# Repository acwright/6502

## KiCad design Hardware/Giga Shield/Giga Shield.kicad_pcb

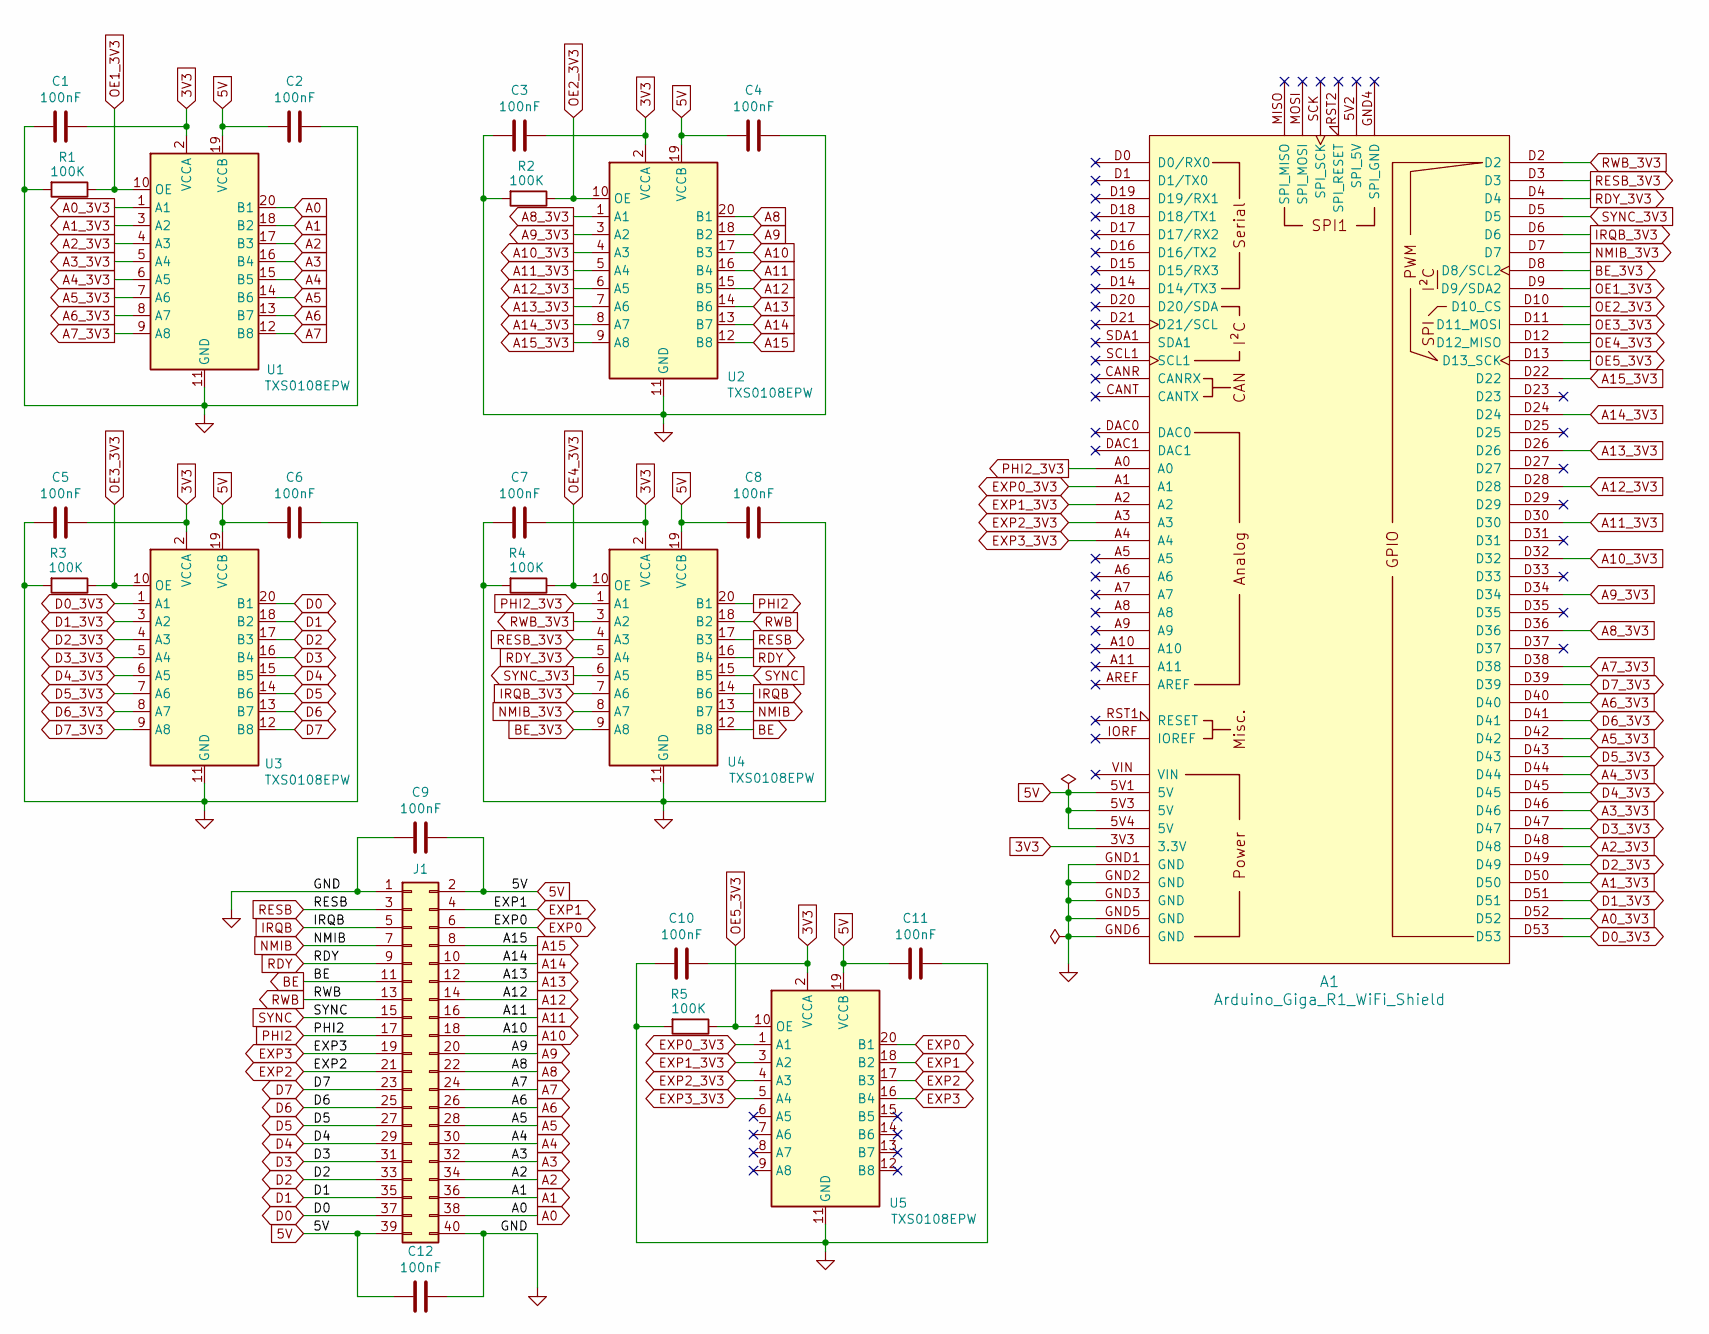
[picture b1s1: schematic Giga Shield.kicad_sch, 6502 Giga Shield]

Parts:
A1: Arduino_Giga_R1_WiFi_Shield
C1, C2, C3, C4, C5, C6, C7, C8, C9, C10, C11, C12: 100nF; C_0805_2012Metric; LCSC C49678
J1: Conn_02x20_Odd_Even; PinHeader_2x20_P2.54mm_Vertical
R1, R2, R3, R4, R5: 100K; R_0805_2012Metric; LCSC C149504
U1, U2, U3, U4, U5: TXS0108EPW; TSSOP-20_4.4x6.5mm_P0.65mm; LCSC C17206

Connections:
3V3: A1.3V3 (3.3V), C1.1, C3.1, C5.1, C7.1, C10.1, U1.2 (VCCA), U2.2 (VCCA), U3.2 (VCCA), U4.2 (VCCA), U5.2 (VCCA)
5V: A1.5V1 (5V), A1.5V3 (5V), A1.5V4 (5V), C2.2, C4.2, C6.2, C8.2, C9.1, C11.2, C12.2, J1.2, J1.39, U1.19 (VCCB), U2.19 (VCCB), U3.19 (VCCB), U4.19 (VCCB), U5.19 (VCCB)
A0: J1.38, U1.20 (B1)
A0_3V3: A1.D52, U1.1 (A1)
A1: J1.36, U1.18 (B2)
A1_3V3: A1.D50, U1.3 (A2)
A2: J1.34, U1.17 (B3)
A2_3V3: A1.D48, U1.4 (A3)
A3: J1.32, U1.16 (B4)
A3_3V3: A1.D46, U1.5 (A4)
A4: J1.30, U1.15 (B5)
A4_3V3: A1.D44, U1.6 (A5)
A5: J1.28, U1.14 (B6)
A5_3V3: A1.D42, U1.7 (A6)
A6: J1.26, U1.13 (B7)
A6_3V3: A1.D40, U1.8 (A7)
A7: J1.24, U1.12 (B8)
A7_3V3: A1.D38, U1.9 (A8)
A8: J1.22, U2.20 (B1)
A8_3V3: A1.D36, U2.1 (A1)
A9: J1.20, U2.18 (B2)
A9_3V3: A1.D34, U2.3 (A2)
A10: J1.18, U2.17 (B3)
A10_3V3: A1.D32, U2.4 (A3)
A11: J1.16, U2.16 (B4)
A11_3V3: A1.D30, U2.5 (A4)
A12: J1.14, U2.15 (B5)
A12_3V3: A1.D28, U2.6 (A5)
A13: J1.12, U2.14 (B6)
A13_3V3: A1.D26, U2.7 (A6)
A14: J1.10, U2.13 (B7)
A14_3V3: A1.D24, U2.8 (A7)
A15: J1.8, U2.12 (B8)
A15_3V3: A1.D22, U2.9 (A8)
BE: J1.11, U4.12 (B8)
BE_3V3: A1.D8 (D8/SCL2), U4.9 (A8)
D0: J1.37, U3.20 (B1)
D0_3V3: A1.D53, U3.1 (A1)
D1: J1.35, U3.18 (B2)
D1_3V3: A1.D51, U3.3 (A2)
D2: J1.33, U3.17 (B3)
D2_3V3: A1.D49, U3.4 (A3)
D3: J1.31, U3.16 (B4)
D3_3V3: A1.D47, U3.5 (A4)
D4: J1.29, U3.15 (B5)
D4_3V3: A1.D45, U3.6 (A5)
D5: J1.27, U3.14 (B6)
D5_3V3: A1.D43, U3.7 (A6)
D6: J1.25, U3.13 (B7)
D6_3V3: A1.D41, U3.8 (A7)
D7: J1.23, U3.12 (B8)
D7_3V3: A1.D39, U3.9 (A8)
EXP0: J1.6, U5.20 (B1)
EXP0_3V3: A1.A1, U5.1 (A1)
EXP1: J1.4, U5.18 (B2)
EXP1_3V3: A1.A2, U5.3 (A2)
EXP2: J1.21, U5.17 (B3)
EXP2_3V3: A1.A3, U5.4 (A3)
EXP3: J1.19, U5.16 (B4)
EXP3_3V3: A1.A4, U5.5 (A4)
GND: A1.GND1 (GND), A1.GND2 (GND), A1.GND3 (GND), A1.GND5 (GND), A1.GND6 (GND), C1.2, C2.1, C3.2, C4.1, C5.2, C6.1, C7.2, C8.1, C9.2, C10.2, C11.1, C12.1, J1.1, J1.40, R1.2, R2.2, R3.2, R4.2, R5.2, U1.11 (GND), U2.11 (GND), U3.11 (GND), U4.11 (GND), U5.11 (GND)
IRQB: J1.5, U4.14 (B6)
IRQB_3V3: A1.D6, U4.7 (A6)
NMIB: J1.7, U4.13 (B7)
NMIB_3V3: A1.D7, U4.8 (A7)
OE1_3V3: A1.D9 (D9/SDA2), R1.1, U1.10 (OE)
OE2_3V3: A1.D10 (D10_CS), R2.1, U2.10 (OE)
OE3_3V3: A1.D11 (D11_MOSI), R3.1, U3.10 (OE)
OE4_3V3: A1.D12 (D12_MISO), R4.1, U4.10 (OE)
OE5_3V3: A1.D13 (D13_SCK), R5.1, U5.10 (OE)
PHI2: J1.17, U4.20 (B1)
PHI2_3V3: A1.A0, U4.1 (A1)
RDY: J1.9, U4.16 (B4)
RDY_3V3: A1.D4, U4.5 (A4)
RESB: J1.3, U4.17 (B3)
RESB_3V3: A1.D3, U4.4 (A3)
RWB: J1.13, U4.18 (B2)
RWB_3V3: A1.D2, U4.3 (A2)
SYNC: J1.15, U4.15 (B5)
SYNC_3V3: A1.D5, U4.6 (A5)

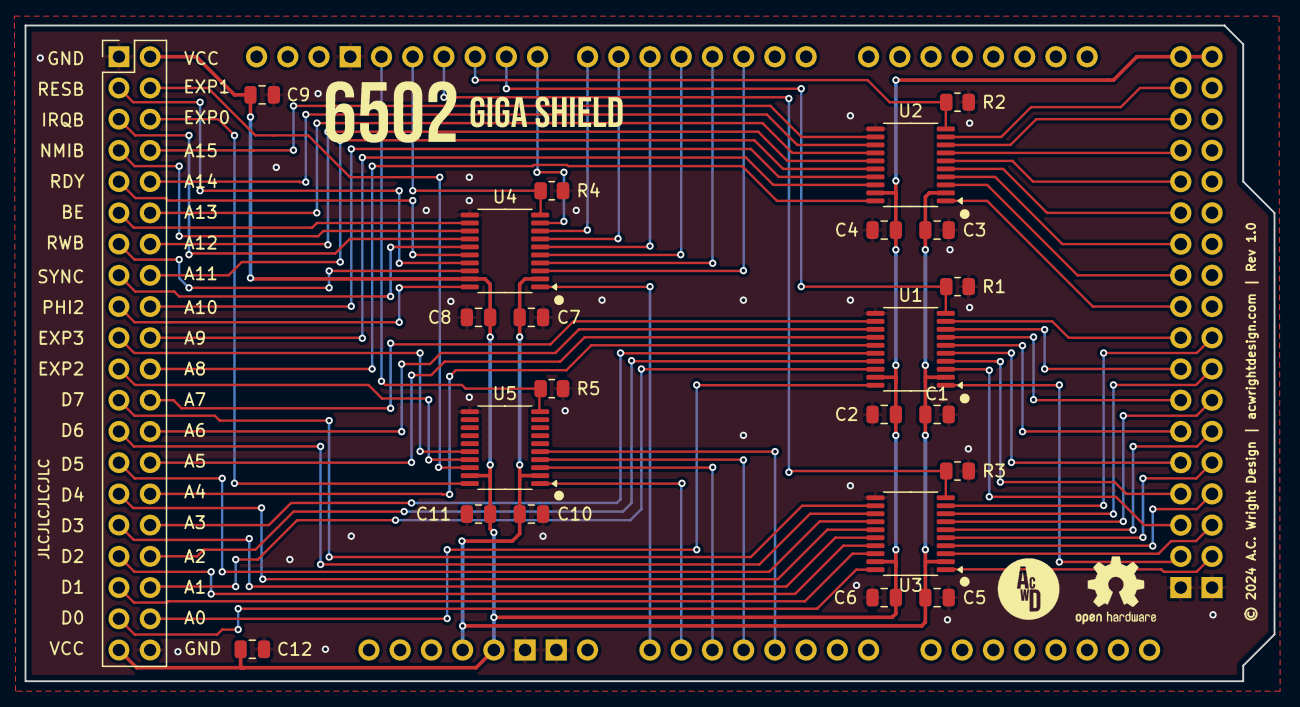
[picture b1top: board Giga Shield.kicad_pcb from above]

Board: 2 copper layers, 101.6 x 53.3 mm, 24 parts (0 on the bottom side), 80 nets.

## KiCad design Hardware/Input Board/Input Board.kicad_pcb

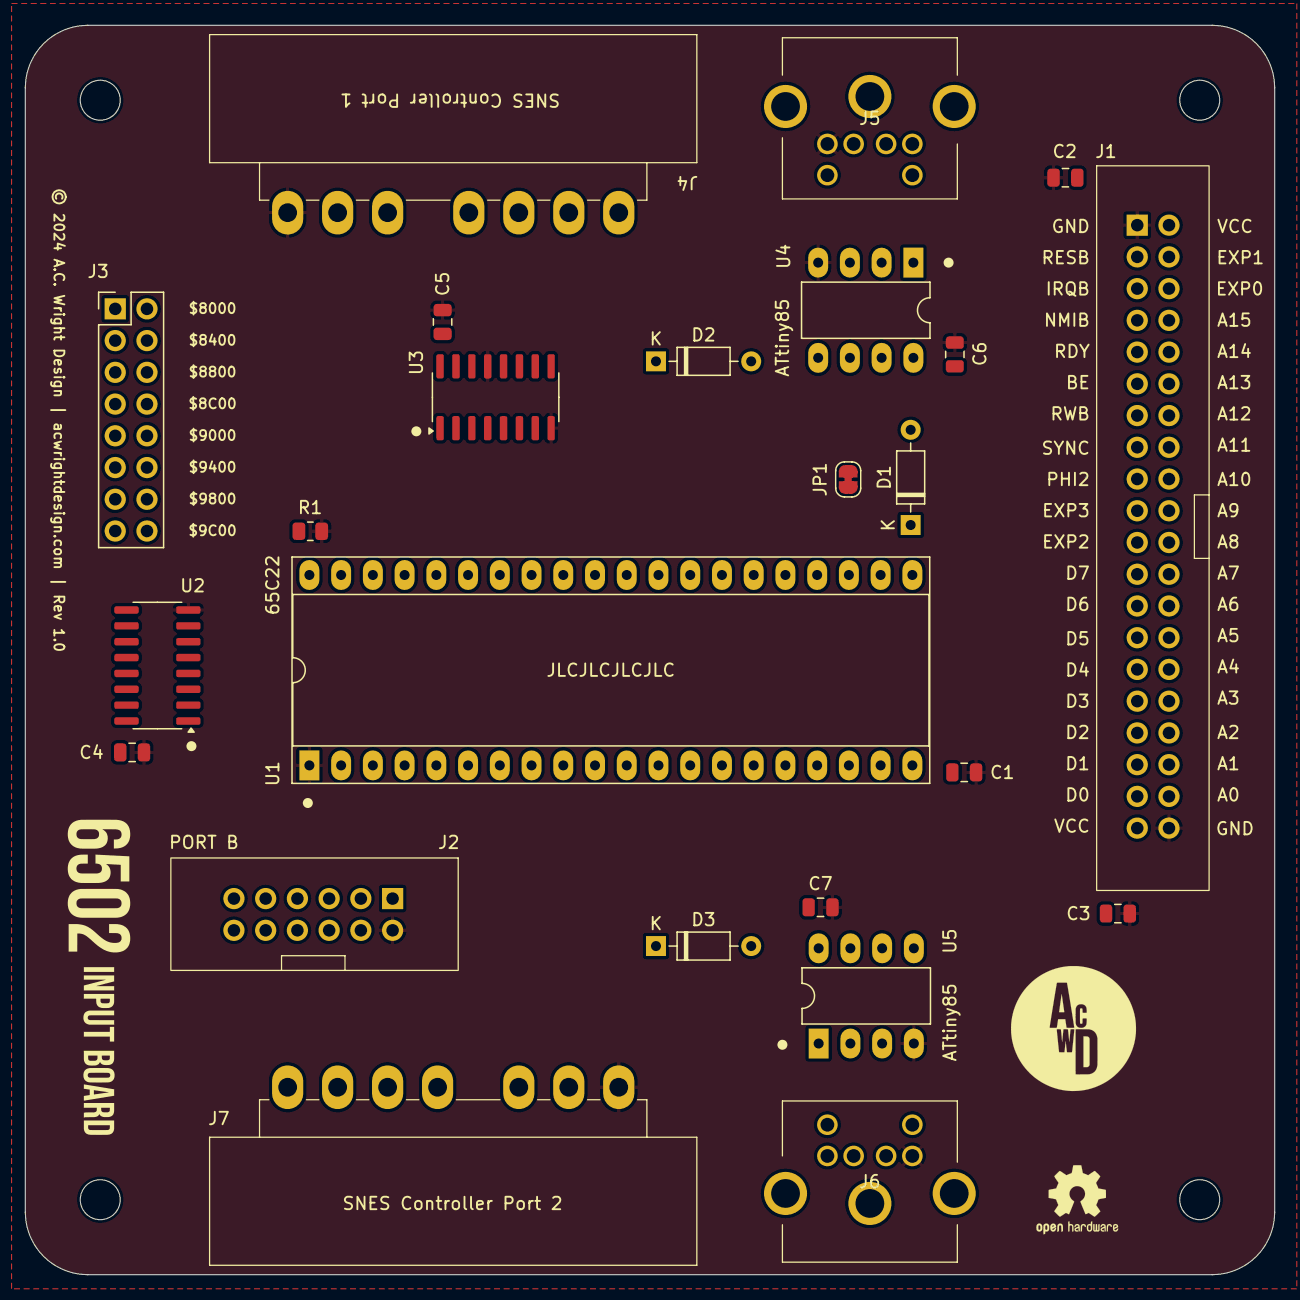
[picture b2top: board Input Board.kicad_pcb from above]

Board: 2 copper layers, 100.0 x 100.0 mm, 28 parts (0 on the bottom side), 62 nets.

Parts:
C1, C2, C3, C4, C5, C6, C7: 100nF; C_0805_2012Metric
D1, D2, D3: D_Schottky; D_DO-35_SOD27_P7.62mm_Horizontal
H1, H2, H3, H4: MountingHole; MountingHole_3.2mm_M3
J1: 6502 Bus; 6502 Bus Connector
J2: PORT B; 6502 GPIO Connector
J3: Conn_02x08_Odd_Even; PinHeader_2x08_P2.54mm_Vertical
J4: SNES Controller Port 1; SNES Controller Port
J5: Keyboard; KMDGX-6S-BS
J6: Mouse; KMDGX-6S-BS
J7: SNES Controller Port 2; SNES Controller Port
JP1: SolderJumper_2_Bridged; SolderJumper-2_P1.3mm_Bridged_RoundedPad1.0x1.5mm
R1: 10k; R_0805_2012Metric
U1: 65C22; DIP-40_W15.24mm_Socket_LongPads
U2: 74HC138; SOIC-16_3.9x9.9mm_P1.27mm
U3: 74HC595; SOIC-16_3.9x9.9mm_P1.27mm
U4, U5: ATtiny85; DIP-8_W7.62mm_LongPads

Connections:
/$8C00: J3.7, U2.12 (~Y3)
/$9C00: J3.15, U2.7 (~Y7)
/$8000: J3.1, U2.15 (~Y0)
/$8400: J3.3, U2.14 (~Y1)
/$8800: J3.5, U2.13 (~Y2)
/$9000: J3.9, U2.11 (~Y4)
/$9400: J3.11, U2.10 (~Y5)
/$9800: J3.13, U2.9 (~Y6)
A0: J1.38, U1.38 (RS0)
A1: J1.36, U1.37 (RS1)
A2: J1.34, U1.36 (RS2)
A3: J1.32, U1.35 (RS3)
A10: J1.18, U2.1 (A0)
A11: J1.16, U2.2 (A1)
A12: J1.14, U2.3 (A2)
A13: J1.12, U2.4 (~E0)
A14: J1.10, U2.5 (~E1)
A15: J1.8, U2.6 (E2)
CA2: U1.39 (CA2), U4.1 (~RESET/PB5), U5.1 (~RESET/PB5)
CB1: J2.11, U1.18 (CB1)
CB2: J2.12, U1.19 (CB2)
CLK: U3.11 (SRCLK), U3.12 (RCLK), U4.5 (AREF/PB0), U5.5 (AREF/PB0)
CSB: J3.2, J3.4, J3.6, J3.8, J3.10, J3.12, J3.14, J3.16, U1.23 (CS2B)
D0: J1.37, U1.33 (D0)
D1: J1.35, U1.32 (D1)
D2: J1.33, U1.31 (D2)
D3: J1.31, U1.30 (D3)
D4: J1.29, U1.29 (D4)
D5: J1.27, U1.28 (D5)
D6: J1.25, U1.27 (D6)
D7: J1.23, U1.26 (D7)
DATA: U3.14 (SER), U4.6 (PB1), U5.6 (PB1)
GND: C1.1, C2.2, C3.1, C4.2, C5.2, C6.2, C7.2, J1.1, J1.40, J2.2, J4.7 (GND), J5.3, J6.3, J7.7 (GND), R1.2, U1.1 (VSS), U2.8 (GND), U3.8 (GND), U3.13 (~OE), U4.4 (GND), U5.4 (GND)
IRQB: D1.2 (A), J1.5, JP1.2 (B)
KBD_CLK: J5.6, U4.7 (PB2)
KBD_DATA: J5.1, U4.2 (XTAL1/PB3)
KBD_INT: D2.2 (A), U4.3 (XTAL2/PB4)
MS_CLK: J6.6, U5.7 (PB2)
MS_DATA: J6.1, U5.2 (XTAL1/PB3)
MS_INT: D3.2 (A), U5.3 (XTAL2/PB4)
unnamed: D1.1 (K), JP1.1 (A), U1.21 (IRQB)
unnamed: D2.1 (K), D3.1 (K), R1.1, U1.40 (CA1)
PA0: U1.2 (PA0), U3.15 (QA)
PA1: U1.3 (PA1), U3.1 (QB)
PA2: U1.4 (PA2), U3.2 (QC)
PA3: U1.5 (PA3), U3.3 (QD)
PA4: U1.6 (PA4), U3.4 (QE)
PA5: U1.7 (PA5), U3.5 (QF)
PA6: U1.8 (PA6), U3.6 (QG)
PA7: U1.9 (PA7), U3.7 (QH)
PB0: J2.4, J4.2 (Clock), J7.2 (Clock), U1.10 (PB0)
PB1: J2.6, J4.3 (Latch), J7.3 (Latch), U1.11 (PB1)
PB2: J2.8, J4.4 (Data), U1.12 (PB2)
PB3: J2.10, J7.4 (Data), U1.13 (PB3)
PB4: J2.9, U1.14 (PB4)
PB5: J2.7, U1.15 (PB5)
PB6: J2.5, U1.16 (PB6)
PB7: J2.3, U1.17 (PB7)
PHI2: J1.17, U1.25 (PHI2)
RESB: J1.3, U1.34 (RESB)
RWB: J1.13, U1.22 (RWB)
VCC: C1.2, C2.1, C3.2, C4.1, C5.1, C6.1, C7.1, J1.2, J1.39, J2.1, J4.1 (VCC), J5.5, J6.5, J7.1 (VCC), U1.20 (VDD), U1.24 (CS1), U2.16 (VCC), U3.10 (~SRCLR), U3.16 (VCC), U4.8 (VCC), U5.8 (VCC)

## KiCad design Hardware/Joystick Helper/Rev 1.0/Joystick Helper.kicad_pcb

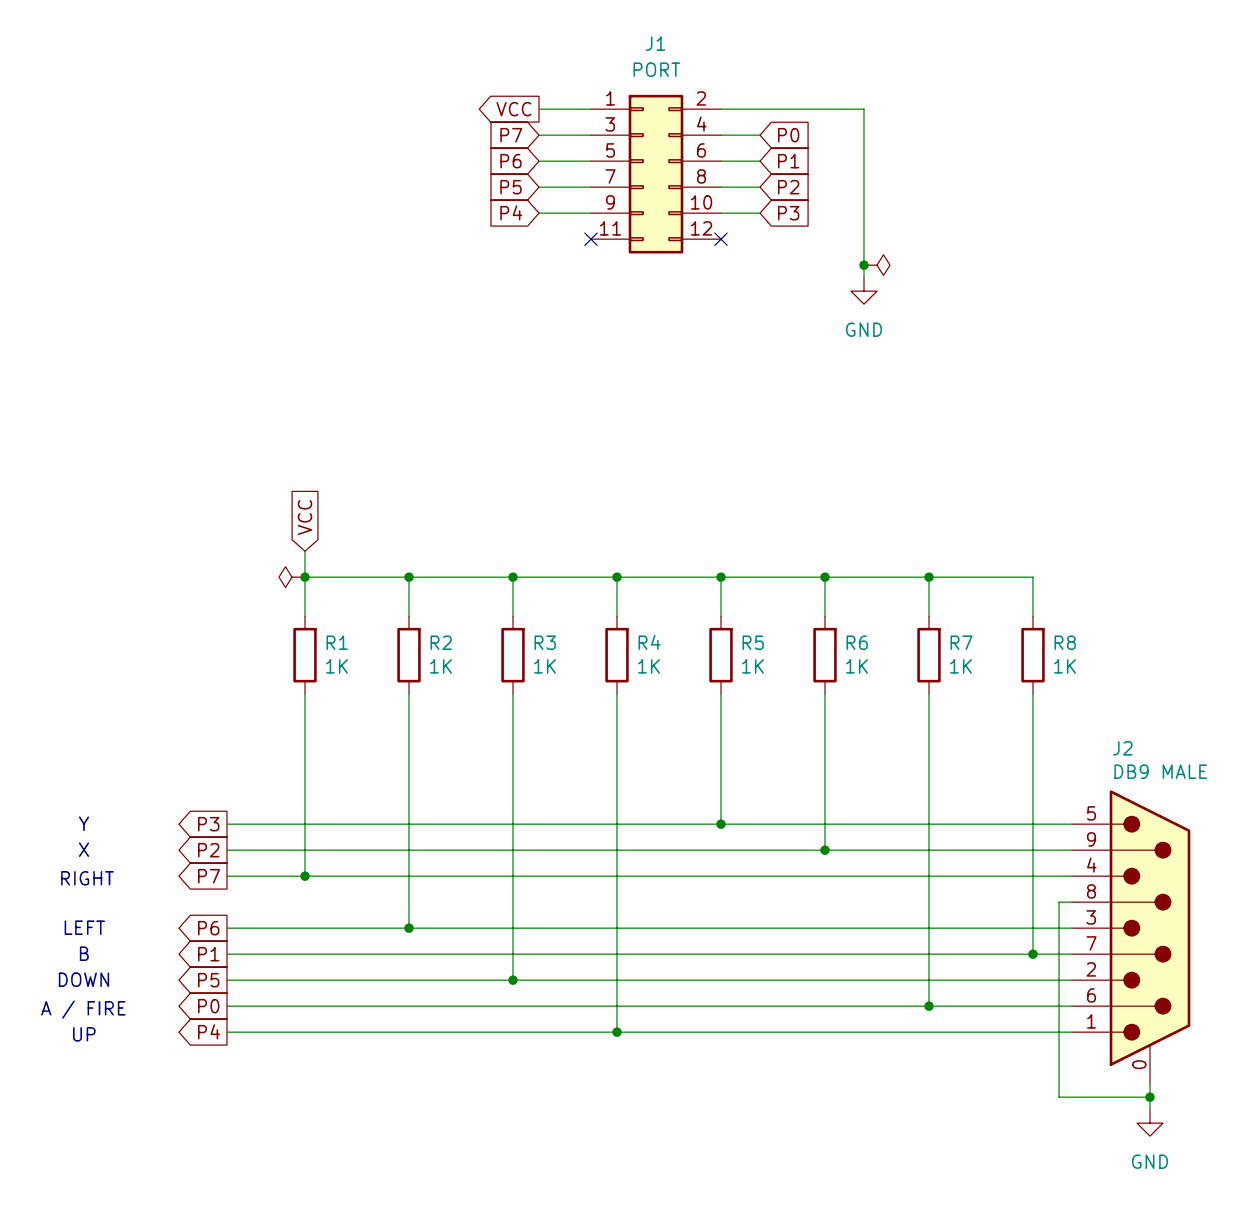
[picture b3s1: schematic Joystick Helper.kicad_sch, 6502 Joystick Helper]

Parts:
J1: PORT; 6502 GPIO Connector
J2: DB9 MALE; DSUB-9_Pins_Horizontal_P2.77x2.84mm_EdgePinOffset7.70mm_Hou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; MPN D09P33E4GX00LF; Digikey 609-1481-ND
R1, R2, R3, R4, R5, R6, R7, R8: 1K; R_Axial_DIN0204_L3.6mm_D1.6mm_P5.08mm_Horizontal

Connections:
GND: J1.2, J2.0 (PAD), J2.8
P0: J1.4, J2.6, R7.1
P1: J1.6, J2.7, R8.1
P2: J1.8, J2.9, R6.1
P3: J1.10, J2.5, R5.1
P4: J1.9, J2.1, R4.1
P5: J1.7, J2.2, R3.1
P6: J1.5, J2.3, R2.1
P7: J1.3, J2.4, R1.1
VCC: J1.1, R1.2, R2.2, R3.2, R4.2, R5.2, R6.2, R7.2, R8.2

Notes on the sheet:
LEFT
DOWN
RIGHT
A / FIRE

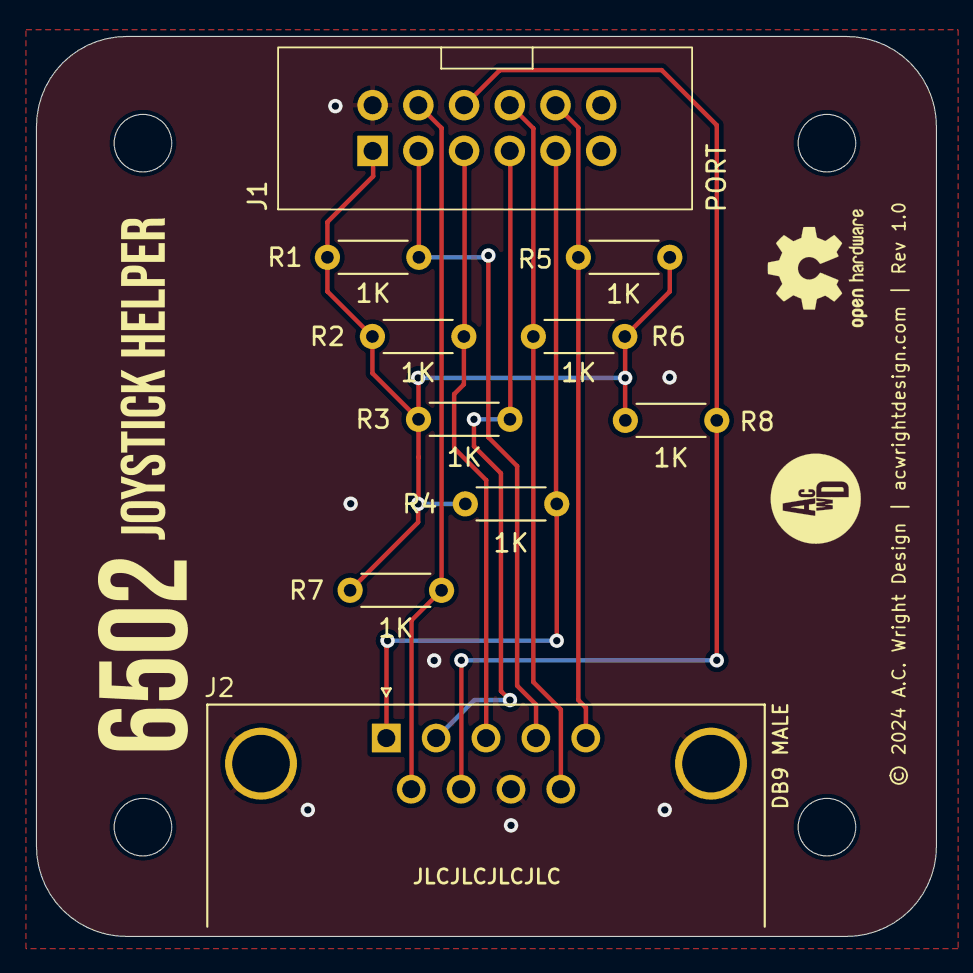
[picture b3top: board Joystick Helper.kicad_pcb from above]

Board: 2 copper layers, 50.0 x 50.0 mm, 14 parts (0 on the bottom side), 10 nets.

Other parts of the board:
H1, H2, H3, H4: MountingHole; MountingHole_3.2mm_M3

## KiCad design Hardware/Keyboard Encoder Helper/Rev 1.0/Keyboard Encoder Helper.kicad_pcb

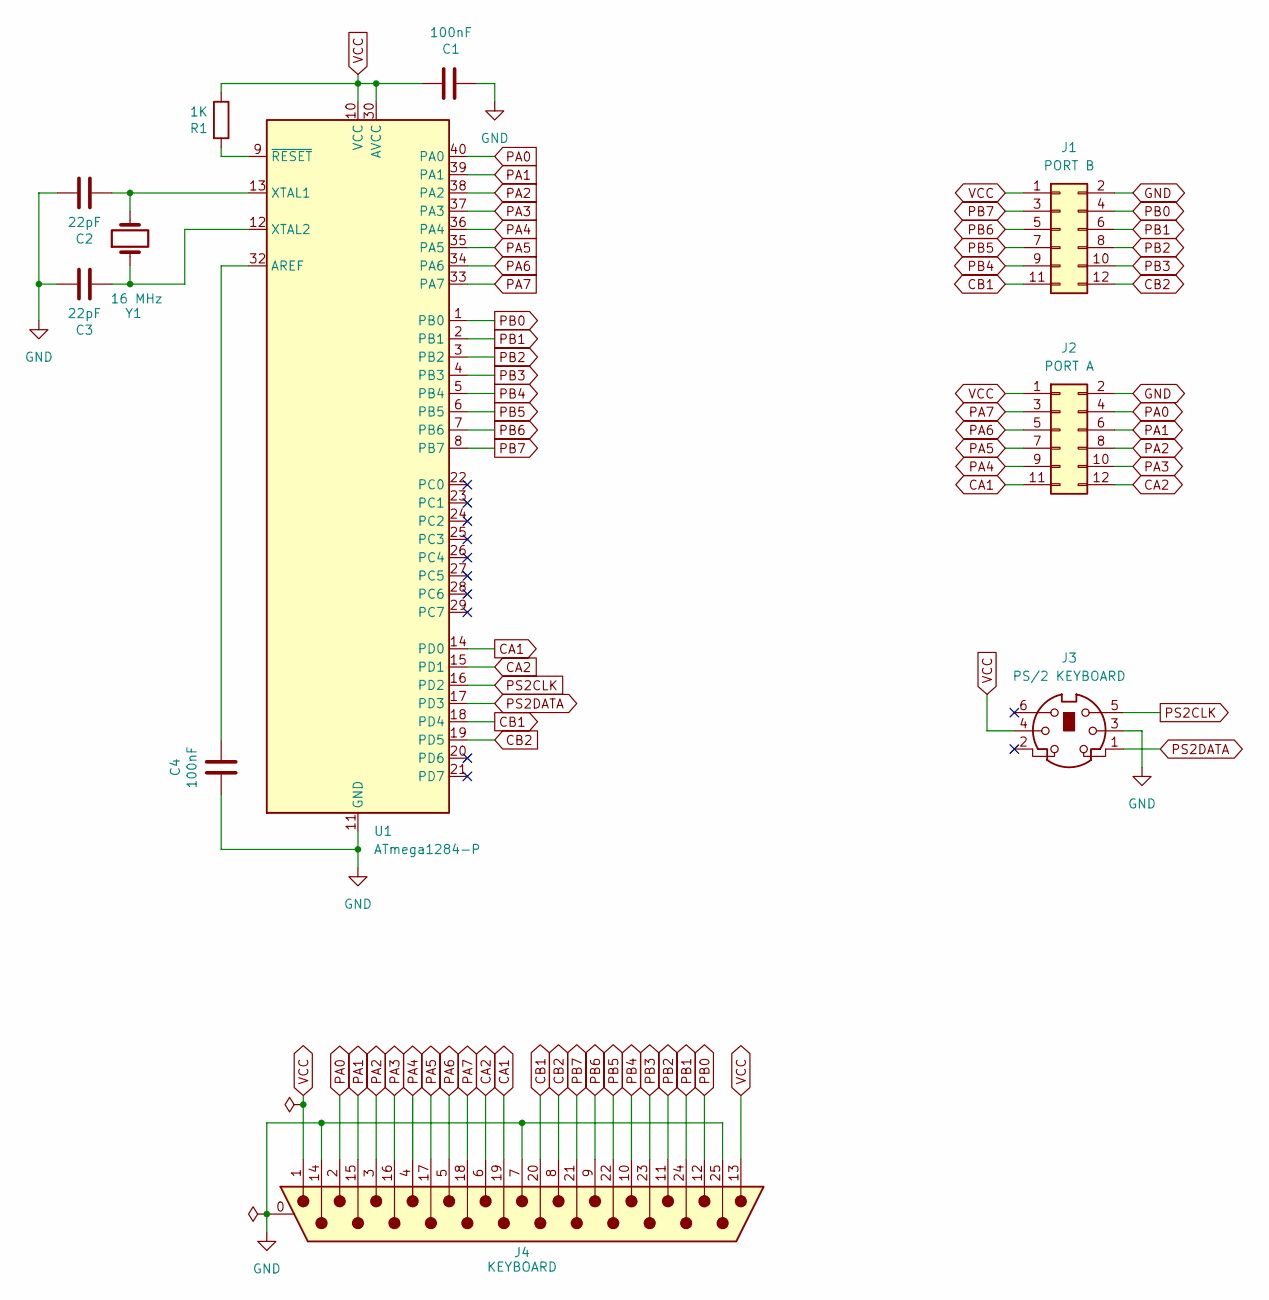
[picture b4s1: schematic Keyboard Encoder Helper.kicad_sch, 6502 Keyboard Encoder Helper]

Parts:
C1, C4: 100nF; C_Disc_D5.0mm_W2.5mm_P2.50mm; LCSC C107114
C2, C3: 22pF; C_Disc_D5.0mm_W2.5mm_P2.50mm; LCSC C107114
J1: PORT B; 6502 GPIO Connector
J2: PORT A; 6502 GPIO Connector
J3: PS/2 KEYBOARD; KMDGX-6S-BS
J4: KEYBOARD; DSUB-25_Pins_Horizontal_P2.77x2.84mm_EdgePinOffset7.70mm_Ho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; MPN D25P33E4GX00LF; Digikey 609-1505-ND
R1: 1K; R_Axial_DIN0204_L3.6mm_D1.6mm_P5.08mm_Horizontal
U1: ATmega1284-P; DIP-40_W15.24mm_Socket_LongPads
Y1: 16 MHz; Crystal_HC49-U_Vertical; Digikey 3155-16M20P2/49US-ND

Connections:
CA1: J2.11, J4.19, U1.14 (PD0)
CA2: J2.12, J4.6, U1.15 (PD1)
CB1: J1.11, J4.20, U1.18 (PD4)
CB2: J1.12, J4.8, U1.19 (PD5)
GND: C1.1, C2.2, C3.2, C4.1, J1.2, J2.2, J3.3, J4.0 (PAD), J4.7, J4.14, J4.25, U1.11 (GND), U1.31 (GND)
unnamed: C4.2, U1.32 (AREF)
unnamed: C2.1, U1.13 (XTAL1), Y1.2
unnamed: C3.1, U1.12 (XTAL2), Y1.1
unnamed: R1.2, U1.9 (~RESET)
PA0: J2.4, J4.2, U1.40 (PA0)
PA1: J2.6, J4.15, U1.39 (PA1)
PA2: J2.8, J4.3, U1.38 (PA2)
PA3: J2.10, J4.16, U1.37 (PA3)
PA4: J2.9, J4.4, U1.36 (PA4)
PA5: J2.7, J4.17, U1.35 (PA5)
PA6: J2.5, J4.5, U1.34 (PA6)
PA7: J2.3, J4.18, U1.33 (PA7)
PB0: J1.4, J4.12, U1.1 (PB0)
PB1: J1.6, J4.24, U1.2 (PB1)
PB2: J1.8, J4.11, U1.3 (PB2)
PB3: J1.10, J4.23, U1.4 (PB3)
PB4: J1.9, J4.10, U1.5 (PB4)
PB5: J1.7, J4.22, U1.6 (PB5)
PB6: J1.5, J4.9, U1.7 (PB6)
PB7: J1.3, J4.21, U1.8 (PB7)
PS2CLK: J3.5, U1.16 (PD2)
PS2DATA: J3.1, U1.17 (PD3)
VCC: C1.2, J1.1, J2.1, J3.4, J4.1, J4.13, R1.1, U1.10 (VCC), U1.30 (AVCC)

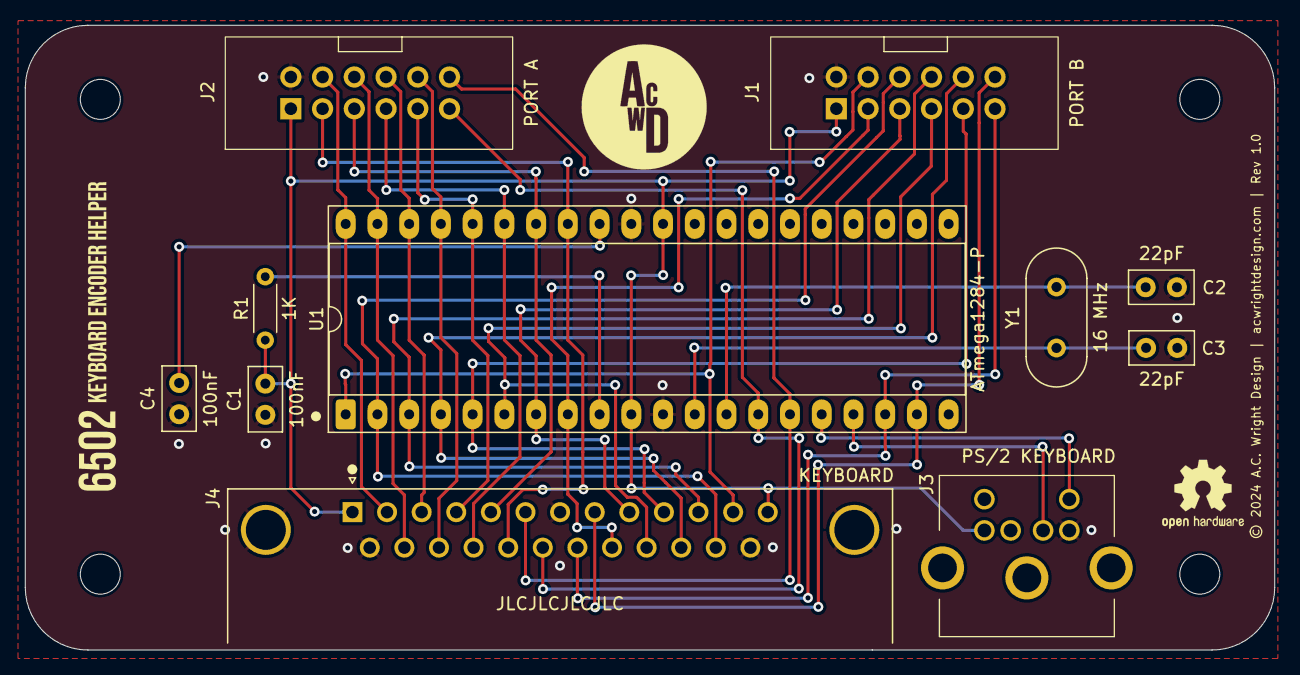
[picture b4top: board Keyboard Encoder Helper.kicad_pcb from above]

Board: 2 copper layers, 100.0 x 50.0 mm, 15 parts (0 on the bottom side), 28 nets.

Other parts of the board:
H1, H2, H3, H4: MountingHole; MountingHole_3.2mm_M3

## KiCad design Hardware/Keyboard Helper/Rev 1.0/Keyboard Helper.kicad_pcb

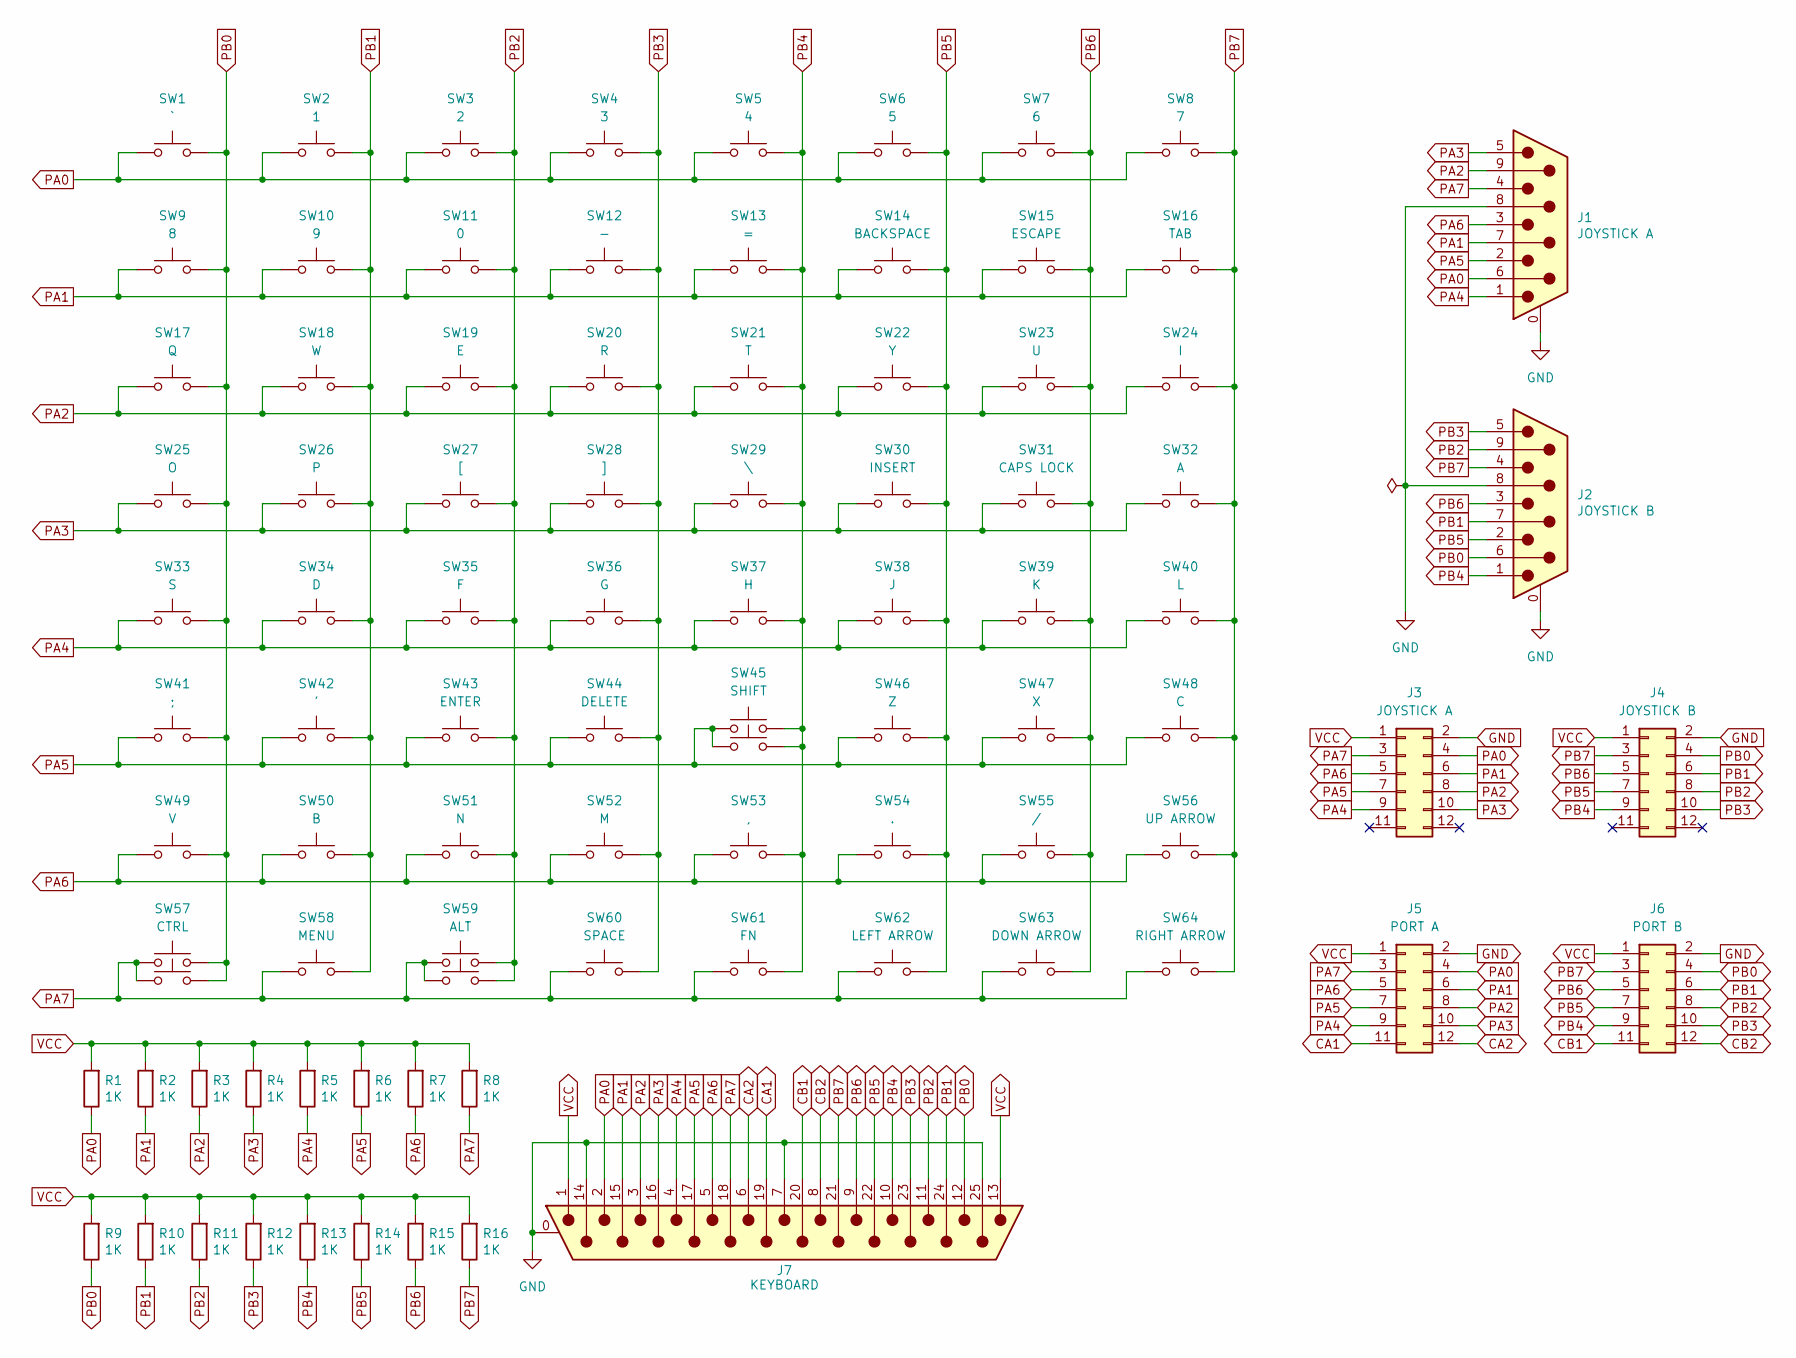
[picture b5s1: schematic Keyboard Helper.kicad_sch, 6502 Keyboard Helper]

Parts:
J1: JOYSTICK A; DSUB-9_Pins_Horizontal_P2.77x2.84mm_EdgePinOffset7.70mm_Hou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; MPN D09P33E4GX00LF; Digikey 609-1481-ND
J2: JOYSTICK B; DSUB-9_Pins_Horizontal_P2.77x2.84mm_EdgePinOffset7.70mm_Hou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; MPN D09P33E4GX00LF; Digikey 609-1481-ND
J3: JOYSTICK A; 6502 GPIO Connector
J4: JOYSTICK B; 6502 GPIO Connector
J5: PORT A; 6502 GPIO Connector
J6: PORT B; 6502 GPIO Connector
J7: KEYBOARD; DSUB-25_Pins_Horizontal_P2.77x2.84mm_EdgePinOffset7.70mm_Ho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; MPN D25P33E4GX00LF; Digikey 609-1505-ND
R1, R2, R3, R4, R5, R6, R7, R8, R9, R10, R11, R12, R13, R14, R15, R16: 1K; R_Axial_DIN0204_L3.6mm_D1.6mm_P5.08mm_Horizontal
SW1: `; SW_Cherry_MX_1.00u_PCB
SW2: 1; SW_Cherry_MX_1.00u_PCB
SW3: 2; SW_Cherry_MX_1.00u_PCB
SW4: 3; SW_Cherry_MX_1.00u_PCB
SW5: 4; SW_Cherry_MX_1.00u_PCB
SW6: 5; SW_Cherry_MX_1.00u_PCB
SW7: 6; SW_Cherry_MX_1.00u_PCB
SW8: 7; SW_Cherry_MX_1.00u_PCB
SW9: 8; SW_Cherry_MX_1.00u_PCB
SW10: 9; SW_Cherry_MX_1.00u_PCB
SW11: 0; SW_Cherry_MX_1.00u_PCB
SW12: -; SW_Cherry_MX_1.00u_PCB
SW13: =; SW_Cherry_MX_1.00u_PCB
SW14: BACKSPACE; SW_Cherry_MX_2.00u_PCB
SW15: ESCAPE; SW_Cherry_MX_1.00u_PCB
SW16: TAB; SW_Cherry_MX_1.50u_PCB
SW17: Q; SW_Cherry_MX_1.00u_PCB
SW18: W; SW_Cherry_MX_1.00u_PCB
SW19: E; SW_Cherry_MX_1.00u_PCB
SW20: R; SW_Cherry_MX_1.00u_PCB
SW21: T; SW_Cherry_MX_1.00u_PCB
SW22: Y; SW_Cherry_MX_1.00u_PCB
SW23: U; SW_Cherry_MX_1.00u_PCB
SW24: I; SW_Cherry_MX_1.00u_PCB
SW25: O; SW_Cherry_MX_1.00u_PCB
SW26: P; SW_Cherry_MX_1.00u_PCB
SW27: [; SW_Cherry_MX_1.00u_PCB
SW28: ]; SW_Cherry_MX_1.00u_PCB
SW29: \; SW_Cherry_MX_1.50u_PCB
SW30: INSERT; SW_Cherry_MX_1.00u_PCB
SW31: CAPS LOCK; SW_Cherry_MX_1.75u_PCB
SW32: A; SW_Cherry_MX_1.00u_PCB
SW33: S; SW_Cherry_MX_1.00u_PCB
SW34: D; SW_Cherry_MX_1.00u_PCB
SW35: F; SW_Cherry_MX_1.00u_PCB
SW36: G; SW_Cherry_MX_1.00u_PCB
SW37: H; SW_Cherry_MX_1.00u_PCB
SW38: J; SW_Cherry_MX_1.00u_PCB
SW39: K; SW_Cherry_MX_1.00u_PCB
SW40: L; SW_Cherry_MX_1.00u_PCB
SW41: ;; SW_Cherry_MX_1.00u_PCB
SW42: '; SW_Cherry_MX_1.00u_PCB
SW43: ENTER; SW_Cherry_MX_2.25u_PCB
SW44: DELETE; SW_Cherry_MX_1.00u_PCB
SW45: SHIFT; SW_Cherry_MX_2.25u_PCB
SW46: Z; SW_Cherry_MX_1.00u_PCB
SW47: X; SW_Cherry_MX_1.00u_PCB
SW48: C; SW_Cherry_MX_1.00u_PCB
SW49: V; SW_Cherry_MX_1.00u_PCB
SW50: B; SW_Cherry_MX_1.00u_PCB
SW51: N; SW_Cherry_MX_1.00u_PCB
SW52: M; SW_Cherry_MX_1.00u_PCB
SW53: ,; SW_Cherry_MX_1.00u_PCB
SW54: .; SW_Cherry_MX_1.00u_PCB
SW55: /; SW_Cherry_MX_1.00u_PCB
SW56: UP ARROW; SW_Cherry_MX_1.00u_PCB
SW57: CTRL; SW_Cherry_MX_1.25u_PCB
SW58: MENU; SW_Cherry_MX_1.00u_PCB
SW59: ALT; SW_Cherry_MX_1.25u_PCB
SW60: SPACE; SW_Cherry_MX_6.25u_PCB
SW61: FN; SW_Cherry_MX_1.25u_PCB
SW62: LEFT ARROW; SW_Cherry_MX_1.00u_PCB
SW63: DOWN ARROW; SW_Cherry_MX_1.00u_PCB
SW64: RIGHT ARROW; SW_Cherry_MX_1.00u_PCB
SW65: R SHIFT; SW_Cherry_MX_2.25u_PCB
SW66: R ALT; SW_Cherry_MX_1.25u_PCB
SW67: R CTRL; SW_Cherry_MX_1.25u_PCB

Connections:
CA1: J5.11, J7.19
CA2: J5.12, J7.6
CB1: J6.11, J7.20
CB2: J6.12, J7.8
GND: J1.0 (PAD), J1.8, J2.0 (PAD), J2.8, J3.2, J4.2, J5.2, J6.2, J7.0 (PAD), J7.7, J7.14, J7.25
PA0: J1.6, J3.4, J5.4, J7.2, R1.1, SW1.1, SW2.1, SW3.1, SW4.1, SW5.1, SW6.1, SW7.1, SW8.1
PA1: J1.7, J3.6, J5.6, J7.15, R2.1, SW9.1, SW10.1, SW11.1, SW12.1, SW13.1, SW14.1, SW15.1, SW16.1
PA2: J1.9, J3.8, J5.8, J7.3, R3.1, SW17.1, SW18.1, SW19.1, SW20.1, SW21.1, SW22.1, SW23.1, SW24.1
PA3: J1.5, J3.10, J5.10, J7.16, R4.1, SW25.1, SW26.1, SW27.1, SW28.1, SW29.1, SW30.1, SW31.1, SW32.1
PA4: J1.1, J3.9, J5.9, J7.4, R5.1, SW33.1, SW34.1, SW35.1, SW36.1, SW37.1, SW38.1, SW39.1, SW40.1
PA5: J1.2, J3.7, J5.7, J7.17, R6.1, SW41.1, SW42.1, SW43.1, SW44.1, SW45.1, SW46.1, SW47.1, SW48.1, SW65.1
PA6: J1.3, J3.5, J5.5, J7.5, R7.1, SW49.1, SW50.1, SW51.1, SW52.1, SW53.1, SW54.1, SW55.1, SW56.1
PA7: J1.4, J3.3, J5.3, J7.18, R8.1, SW57.1, SW58.1, SW59.1, SW60.1, SW61.1, SW62.1, SW63.1, SW64.1, SW66.1, SW67.1
PB0: J2.6, J4.4, J6.4, J7.12, R9.1, SW1.2, SW9.2, SW17.2, SW25.2, SW33.2, SW41.2, SW49.2, SW57.2, SW67.2
PB1: J2.7, J4.6, J6.6, J7.24, R10.1, SW2.2, SW10.2, SW18.2, SW26.2, SW34.2, SW42.2, SW50.2, SW58.2
PB2: J2.9, J4.8, J6.8, J7.11, R11.1, SW3.2, SW11.2, SW19.2, SW27.2, SW35.2, SW43.2, SW51.2, SW59.2, SW66.2
PB3: J2.5, J4.10, J6.10, J7.23, R12.1, SW4.2, SW12.2, SW20.2, SW28.2, SW36.2, SW44.2, SW52.2, SW60.2
PB4: J2.1, J4.9, J6.9, J7.10, R13.1, SW5.2, SW13.2, SW21.2, SW29.2, SW37.2, SW45.2, SW53.2, SW61.2, SW65.2
PB5: J2.2, J4.7, J6.7, J7.22, R14.1, SW6.2, SW14.2, SW22.2, SW30.2, SW38.2, SW46.2, SW54.2, SW62.2
PB6: J2.3, J4.5, J6.5, J7.9, R15.1, SW7.2, SW15.2, SW23.2, SW31.2, SW39.2, SW47.2, SW55.2, SW63.2
PB7: J2.4, J4.3, J6.3, J7.21, R16.1, SW8.2, SW16.2, SW24.2, SW32.2, SW40.2, SW48.2, SW56.2, SW64.2
VCC: J3.1, J4.1, J5.1, J6.1, J7.1, J7.13, R1.2, R2.2, R3.2, R4.2, R5.2, R6.2, R7.2, R8.2, R9.2, R10.2, R11.2, R12.2, R13.2, R14.2, R15.2, R16.2

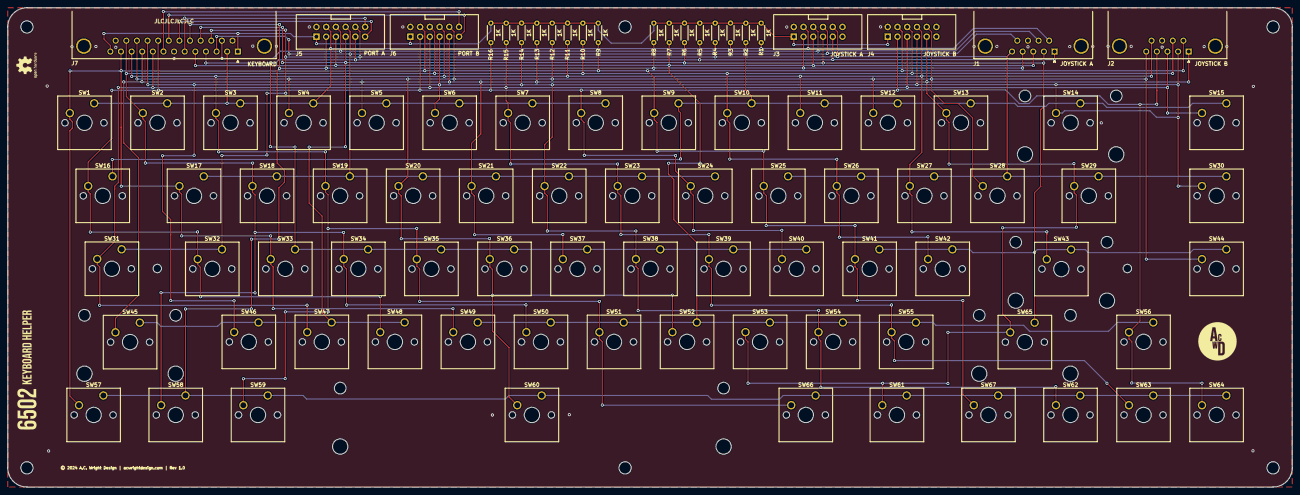
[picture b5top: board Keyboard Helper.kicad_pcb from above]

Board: 2 copper layers, 335.0 x 125.0 mm, 98 parts (0 on the bottom side), 22 nets.

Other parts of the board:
H1, H2, H2#2, H2#3, H3#3, H4: MountingHole; MountingHole_3.2mm_M3
H3, H3#2: MountingHole; MountingHole_2.2mm_M2

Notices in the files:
Hardware/Giga Shield/Giga Shield.kicad_pcb:
© 2024 A.C. Wright Design | acwrightdesign.com | Rev 1.0
